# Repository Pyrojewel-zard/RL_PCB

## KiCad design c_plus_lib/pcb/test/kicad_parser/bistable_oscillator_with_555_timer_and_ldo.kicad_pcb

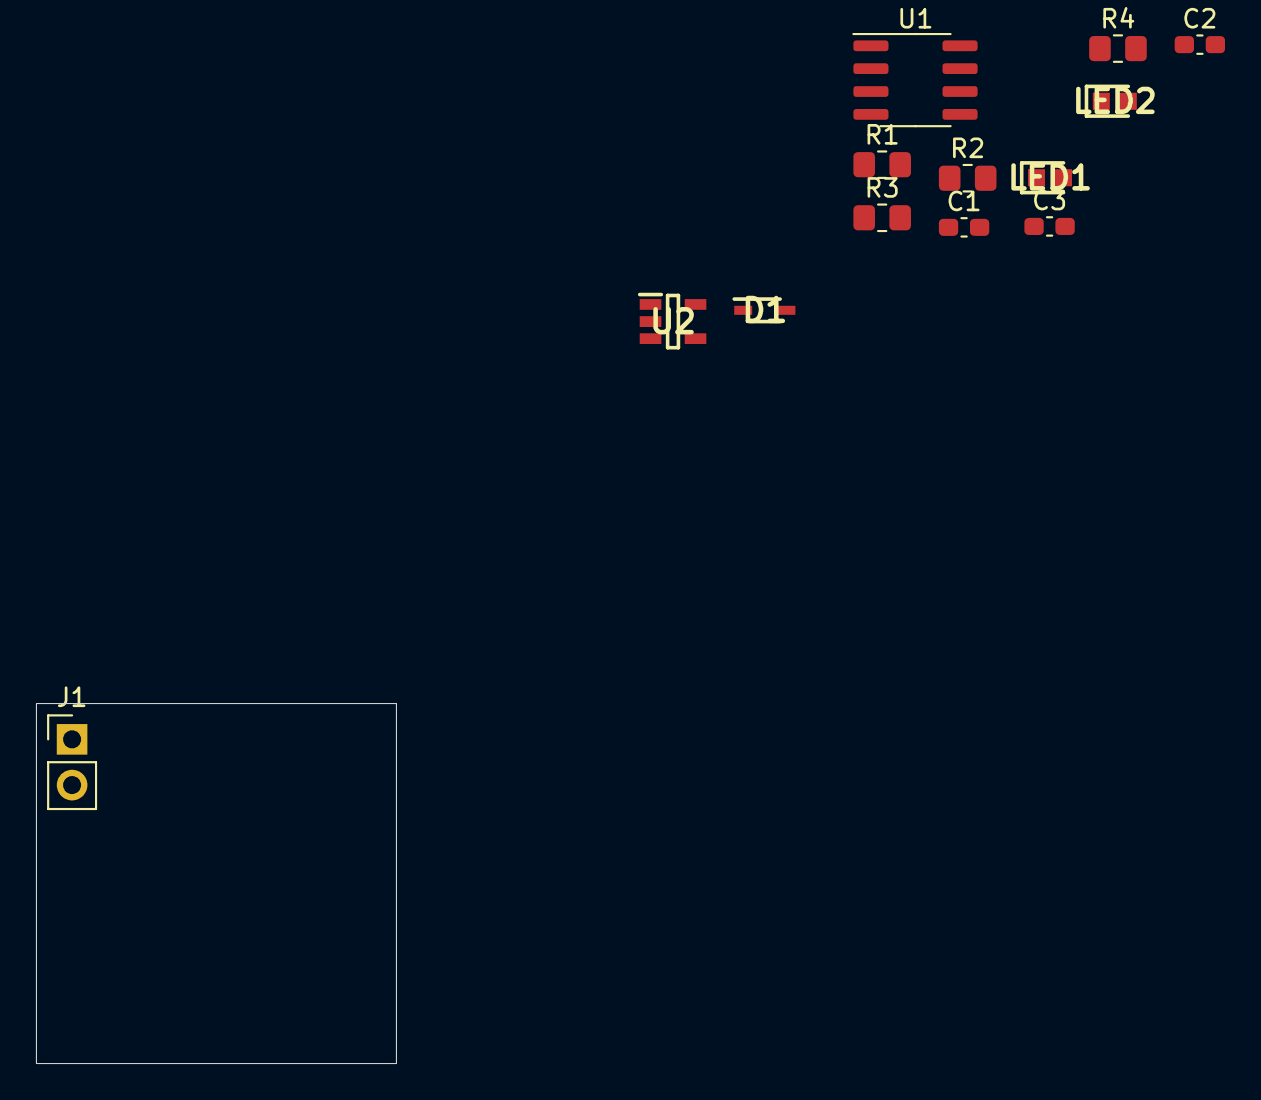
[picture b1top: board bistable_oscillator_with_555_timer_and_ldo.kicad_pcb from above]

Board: 2 copper layers, 20.0 x 20.0 mm, 13 parts (0 on the bottom side), 9 nets, no tracks yet.

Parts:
C1, C2, C3: 1uF; C_0603_1608Metric_Pad1.08x0.95mm_HandSolder
D1: NSR0530HT1G; SOD2512X110N
J1: Conn_01x02_Male; PinHeader_1x02_P2.54mm_Vertical
LED1, LED2: 150060VS75000; LEDC1608X80N
R1, R4: 2k; R_0805_2012Metric_Pad1.20x1.40mm_HandSolder
R2: 47k; R_0805_2012Metric_Pad1.20x1.40mm_HandSolder
R3: 120k; R_0805_2012Metric_Pad1.20x1.40mm_HandSolder
U1: NE555D; SOIC-8_3.9x4.9mm_P1.27mm
U2: TPS7A2033PDBVR; SOT95P280X145-5N

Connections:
+3V3: C2.1, R1.1, R2.1, U1.4, U1.8, U2.5
GND: C1.2, C2.2, C3.2, J1.2, LED1.1, LED2.1, U1.1, U2.2
unnamed: C1.1, D1.1, U2.1, U2.3
unnamed: C3.1, R3.2, U1.2, U1.6
unnamed: D1.2, J1.1
unnamed: LED1.2, R1.2
unnamed: LED2.2, R4.2
unnamed: R2.2, R3.1, U1.7
unnamed: R4.1, U1.3

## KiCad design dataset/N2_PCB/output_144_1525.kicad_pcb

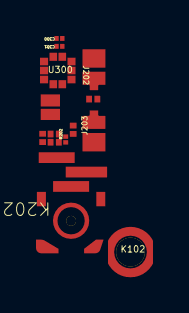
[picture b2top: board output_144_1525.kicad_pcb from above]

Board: 2 copper layers, 14 parts (0 on the bottom side), 7 nets, no tracks yet.

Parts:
C204: CAP_NP_CAP0201-HT0_33_33PF; CAP0201-HT0_33
C300, C301: CAP_NP_CAP01005_HT0_22_S0_38_0.; CAP01005_HT0_22_S0_38
EM200, EM201: CAP_NP_CAP0201-HT0_33_100PF; CAP0201-HT0_33
J110: KEY_2P_ANT_1_0X1_7_P2_HT1_45_HD; ANT_1_0X1_7_P2_HT1_45_HD
J202, J203: KEY_2P_ANT_2_7X1_2_P2_HT2_15_HD; ANT_2_7X1_2_P2_HT2_15_HD
K102: NUT_PAD-RING-TYPE-C_N2_PAD-RING; PAD-RING-TYPE-C_N2
K202: NUT_STIFFER-STEEL-MIC_N2_STIFFE; STIFFER-STEEL-MIC_N2
R202: RES_RES01005_HT0_15_S0_38_0OHM; RES01005_HT0_15_S0_38
R203, R204: RES_RES0201-HT0_23_HD_0OHM; RES0201-HT0_23_HD
U300: BMP580_HLGASQ2_0_PS0_5-HT0_8_P1; HLGASQ2_0_PS0_5-HT0_8_P10_HD

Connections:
CDC_MIC3_N: C204.2, R204.2
CDC_MIC3_P: C204.1, R203.2
GND: C300.2, C301.2, EM200.2, EM201.2, J110.1, J110.2, K102.1, K202.1, R202.2, U300.3, U300.5, U300.7, U300.8, U300.9
HAP_OUT_M: EM200.1, J203.1, J203.2
HAP_OUT_P: EM201.1, J202.1, J202.2
N17757331: R202.1, R204.1
VREG_L1B_1P8: C300.1, C301.1, U300.1, U300.6, U300.10

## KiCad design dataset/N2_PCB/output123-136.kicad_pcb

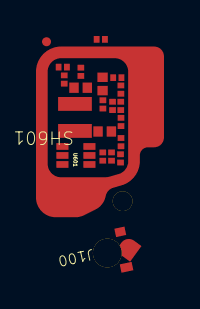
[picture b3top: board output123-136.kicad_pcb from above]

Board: 2 copper layers, 21 parts (0 on the bottom side), 7 nets, no tracks yet.

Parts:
A144: RES_RES0201-HT0_23_HD_0OHM; RES0201-HT0_23_HD
C612: CAP_NP_CAP0201-HT0_33_10PF; CAP0201-HT0_33
C613, C623: CAP_NP_CAP0402-HT0_7_10UF; CAP0402-HT0_7
C614: CAP_NP_CAP0402-HT0_7_22UF; CAP0402-HT0_7
C615, C616, C617, C621, C622: CAP_NP_CAP0201-HT0_35_1UF; CAP0201-HT0_35
C619: CAP_NP_CAP0201-HT0_39_1UF; CAP0201-HT0_39
C620: CAP_NP_CAP0201-HT0_33_0.47UF; CAP0201-HT0_33
J100: SPRING_3P_ANT_2_6X2_99_P3_HT0_5; ANT_2_6X2_99_P3_HT0_58_HD
L600: INDUCTOR_IND2_0X1_6_P1_5_HT1_0_; IND2_0X1_6_P1_5_HT1_0_HD
R601: RES_RES0201-HT0_23_HD_75K; RES0201-HT0_23_HD
R602: RES_RES0201-HT0_23_HD_90.9KOHM; RES0201-HT0_23_HD
R603, R606: RES_NM_RES0201-HT0_28_HD_NM_NM; RES0201-HT0_28_HD_NM
R604: RES_RES0201-HT0_23_HD_10KOHM; RES0201-HT0_23_HD
SH601: SHIELDING_KINE-SHIELDING-FRAME_; KINE-SHIELDING-FRAME_N2
U601: WD10721_DFNSQ1_6_PS0_5_HT0_6_P6; DFNSQ1_6_PS0_5_HT0_6_P6_HD

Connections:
GND: C613.2, C614.2, C615.2, C616.2, C617.2, C619.2, C620.2, C621.2, C622.2, C623.2, R602.2, SH601.1, U601.2
N17753229: J100.1, J100.2, J100.3
N17988891: L600.1, U601.4
N17989092: C612.1, R601.1, R602.1, U601.1
OLED_DVDD: C612.2, C614.1, C621.1, C623.1, L600.2, R601.2, R606.1
TP_1P8: C620.1, R603.2, R604.2
VPH_PWR: C613.1, U601.3

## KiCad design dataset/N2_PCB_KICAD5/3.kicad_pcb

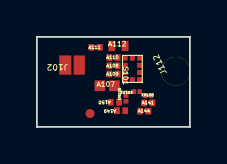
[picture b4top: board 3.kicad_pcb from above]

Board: 2 copper layers, 8.5 x 5.0 mm, 16 parts (0 on the bottom side), 10 nets, no tracks yet.

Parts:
A107: INDUCTOR_IND0402CS-HT0_6_FPC_S_; IND0402CS-HT0_6_FPC_S_1
A108: CAP_NP_CAP0201-HT0_33_1.6PF; CAP0201-HT0_33_24
A109: CAP_NP_CAP0201-HT0_33_2.7PF; CAP0201-HT0_33_26
A110: INDUCTOR_IND0201-HT0_35_15NH; IND0201-HT0_35_7
A111: CAP_NP_CAP0201-HT0_33_33PF; CAP0201-HT0_33_23
A112: INDUCTOR_IND0402CS-HT0_6_10NH; IND0402CS-HT0_6_4
A141: RES_RES0201-HT0_23_HD_0OHM; RES0201-HT0_23_HD_27
A144: RES_RES0201-HT0_23_HD_0OHM; RES0201-HT0_23_HD_28
A149: RES_RES0201-HT0_23_HD_10OHM; RES0201-HT0_23_HD_32
A150: CAP_NP_CAP0201-HT0_33_100NF; CAP0201-HT0_33_25
EM100: RES_NM_RES01005_HT0_15_S0_38_NM; RES01005_HT0_15_S0_38_NM_1
EM101: RES_NM_RES01005_HT0_15_S0_38_NM; RES01005_HT0_15_S0_38_NM_2
EM105: CAP_NM_CAP01005_HT0_22_NM_NM; CAP01005_HT0_22_NM_3
J102: KEY_2P_ANT_1_7X1_0_P2_HT1_35_HD; ANT_1_7X1_0_P2_HT1_35_HD_1
J112: ANT_PIN_ANT_HG_F1_XM-217-XC-186; ANT_HG_F1_1
S101: QM13344_SMT1_1X1_5_HT0_45_10P_H; SMT1_1X1_5_HT0_45_10P_HD_1

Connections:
GND: A112.2, A150.2, EM100.2, EM101.2, EM105.2, S101.5, S101.10
N17753661: A149.2, A150.1, EM105.1, S101.3, S101.4
N17753743: A111.1, J102.1, J102.2
N17753749: A107.1, A108.1, A109.1, A110.1, A111.2, A112.1
N17753816: A109.2, S101.8
N17753880: A108.2, S101.7
N17753882: A141.1, EM100.1, S101.2
N17753954: A144.1, EM101.1, S101.1
N17837242: A110.2, S101.6
N17837274: A107.2, S101.9

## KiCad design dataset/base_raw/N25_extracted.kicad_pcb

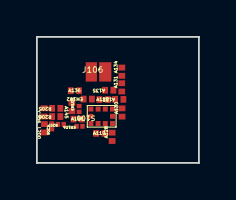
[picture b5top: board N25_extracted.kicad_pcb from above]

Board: 2 copper layers, 9.0 x 7.0 mm, 22 parts (0 on the bottom side), 15 nets, no tracks yet.

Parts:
A118: INDUCTOR_IND0201-HT0_35_11NH; IND0201-HT0_35_2
A119: INDUCTOR_IND0201-HT0_35_5.6NH; IND0201-HT0_35_3
A122: INDUCTOR_IND0201-HT0_35_1NH; IND0201-HT0_35_1
A128: INDUCTOR_IND0201-HT0_42_3NH; IND0201-HT0_42_1
A130: CAP_NP_CAP0201-HT0_33_0.4PF; CAP0201-HT0_33_1
A131: RES_RES0201-HT0_23_HD_0OHM; RES0201-HT0_23_HD_1
A134: CAP_NM_CAP0201-HT0_33_NM_NM; CAP0201-HT0_33_NM_1
A135: CAP_NM_CAP0201-HT0_33_NM_NM; CAP0201-HT0_33_NM_2
A136: RES_RES0201-HT0_23_HD_0OHM; RES0201-HT0_23_HD_4
A145: RES_RES0201-HT0_23_HD_0OHM; RES0201-HT0_23_HD_2
A146: RES_RES0201-HT0_23_HD_0OHM; RES0201-HT0_23_HD_3
C205: CAP_NP_CAP0201-HT0_33_33PF; CAP0201-HT0_33_4
C206: CAP_NP_CAP01005_HT0_22_S0_38_0.; CAP01005_HT0_22_S0_38_1
EM102: CAP_NP_CAP0201-HT0_33_100PF; CAP0201-HT0_33_3
EM103: CAP_NM_CAP01005_HT0_22_NM_NM; CAP01005_HT0_22_NM_1
EM104: CAP_NM_CAP01005_HT0_22_NM_NM; CAP01005_HT0_22_NM_2
J106: KEY_2P_ANT_1_0X1_7_P2_HT1_45_HD; ANT_1_0X1_7_P2_HT1_45_HD_1
L200: INDUCTOR_IND0201-HT0_35_180NH; IND0201-HT0_35_4
R205: RES_RES0201-HT0_23_HD_0OHM; RES0201-HT0_23_HD_5
R206: RES_RES0201-HT0_23_HD_0OHM; RES0201-HT0_23_HD_6
R207: RES_RES01005_HT0_15_S0_38_0OHM; RES01005_HT0_15_S0_38_1
S100: QM13145_SMT1_2X1_6_PS0_4-HT0_5_; SMT1_2X1_6_PS0_4-HT0_5_P10_H6C

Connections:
CDC_MIC4_N: C205.2, R206.2
CDC_MIC4_P: C205.1, R205.2
GND: A118.1, A119.1, A128.1, A134.2, A135.2, C206.2, EM102.2, EM103.2, EM104.2, J106.1, J106.2, R207.2, S100.7
N17753078: A122.1, A130.2, A131.1, A135.1
N17753084: A122.2, S100.1
N17753221: A119.2, S100.8
N17753329: A118.2, S100.2
N17753375: A128.2, S100.9
N17753406: A136.2, EM102.1, S100.3, S100.4
N17753412: A130.1, S100.10
N17753435: A145.2, EM103.1, S100.5
N17753447: A146.2, EM104.1, S100.6
N17753582: A131.2, A134.1
N17757493: R206.1, R207.1
WCD_MIC_BIAS4: C206.1, L200.1

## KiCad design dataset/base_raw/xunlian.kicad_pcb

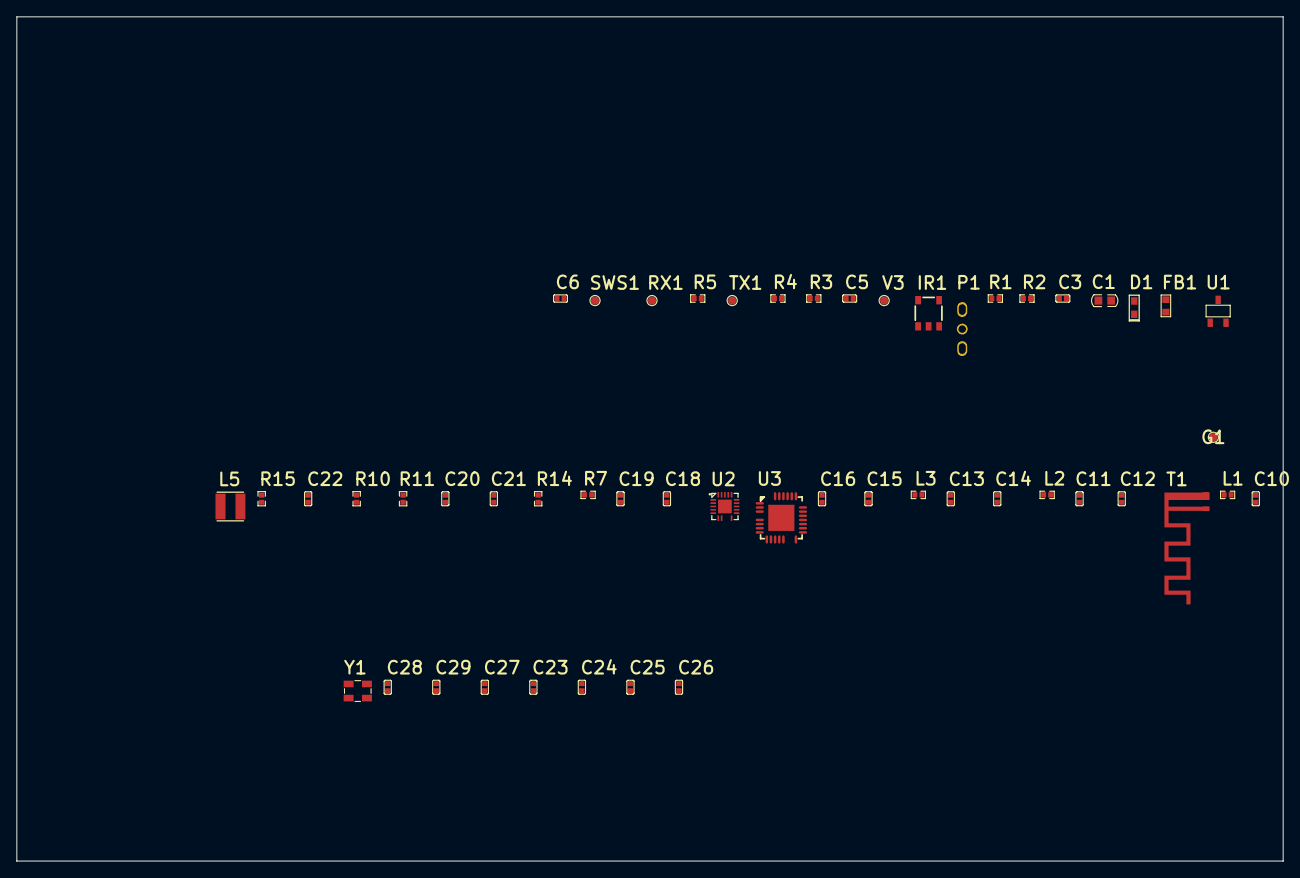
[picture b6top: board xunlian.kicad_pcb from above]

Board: 2 copper layers, 152.4 x 101.6 mm, 51 parts (0 on the bottom side), 39 nets, no tracks yet.

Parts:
C1: 10uF/16V; C0603
C3, C13, C21, C28: 10uF; C0402
C5, C14, C29: 100nF; C0402
C6: 10nF; C0402
C10: 220pF; C0402
C11: 2.2uF; C0402
C12, C16, C18, C22, C24, C25, C26, C27: 1uF; C0402
C15: 18pF; C0402
C19, C20: 1nF; C0402
C23: 33nF; C0402
D1: PT19-21C; LED0603
FB1: GZ1608; R0603
G1: GND; D
IR1: LF0038Q; SMT-IRM
L1: 0R; R0402
L2: NC/1.3nH; R0402
L3: 1nH; R0402
L5: 47uH; L3015
P1: 3P; 3P-2.54
R1, R5: 100R; R0402
R2: 39K; R0402
R3: 47k; R0402
R4, R11: 1K; R0402
R7, R14: 10k; R0402
R10, R15: 0; R0402
RX1: T; D
SWS1: RST; D
T1: TP; BLE_ANT_M
TX1: R; D
U1: LR8103A-T33; SOT23-3-L
U2: XBR818; QFN20_3x3
U3: TLSR8359F512ET32; QFN32
V3: 3V3; D
Y1: 32MHz; SMD3225

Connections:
1V2: C11.1, C12.1, C28.1, C29.1, U3.12, U3.28
3.3V: C3.1, C13.1, C14.2, C22.1, C26.1, D1.2, R1.2, R2.2, R14.1, U1.2, U2.18, U3.9, U3.18, U3.19, V3.1
5V: FB1.1, P1.3
AD: C23.1, R15.2, U3.6
CDS: C5.1, D1.1, R3.2, U3.16
GND: C1.2, C3.2, C5.2, C6.1, C11.2, C12.2, C13.2, C14.1, C15.2, C16.2, C18.2, C19.2, C21.2, C22.2, C23.2, C24.2, C25.2, C26.2, C27.2, C28.2, C29.2, G1.1, IR1.4, L3.2, P1.1, R3.1, R7.1, R10.1, U1.1, U2.5, U2.17, U2.21, U3.7, U3.33, Y1.2, Y1.4
I2C_SCL: U2.12, U3.21
I2C_SDA: U2.11, U3.20
IR: C6.2, R5.1, U3.23
MCU-OUT: R4.1, U3.1
NetC1_1: C1.1, FB1.2, U1.3
NetC10_1: C10.1, L2.2, U3.27
NetC10_2: C10.2, L1.1
NetC15_1: C15.1, L2.1, U3.26
NetC18_1: C18.1, U2.3
NetC19_1: C19.1, U2.2
NetC20_1: C20.1, R15.1, U2.20
NetC20_2: C20.2, R11.2, U2.1
NetC21_1: C21.1, R11.1
NetC24_1: C24.1, U2.19
NetC25_1: C25.1, U3.8
NetC27_1: C27.1, U3.13
NetIR1_3: IR1.3, R2.1, R5.2
NetIR1_5: IR1.5, R1.1
NetL1_2: L1.2, T1.1
NetL5_1: L5.1, U3.11
NetL5_2: L5.2, U3.10
NetR7_2: R7.2, U2.14
NetR14_2: R14.2, U2.13
NetU2_15: U2.15, U2.16
O: P1.2, R4.2
RF_TX: L3.1, U2.6
RST: C16.1, U3.25
RX: RX1.1, U3.3
SWS: SWS1.1, U3.5
TX: TX1.1, U3.2
VRE: R10.2, U3.22
XTAL1: U3.29, Y1.3
XTAL2: U3.30, Y1.1

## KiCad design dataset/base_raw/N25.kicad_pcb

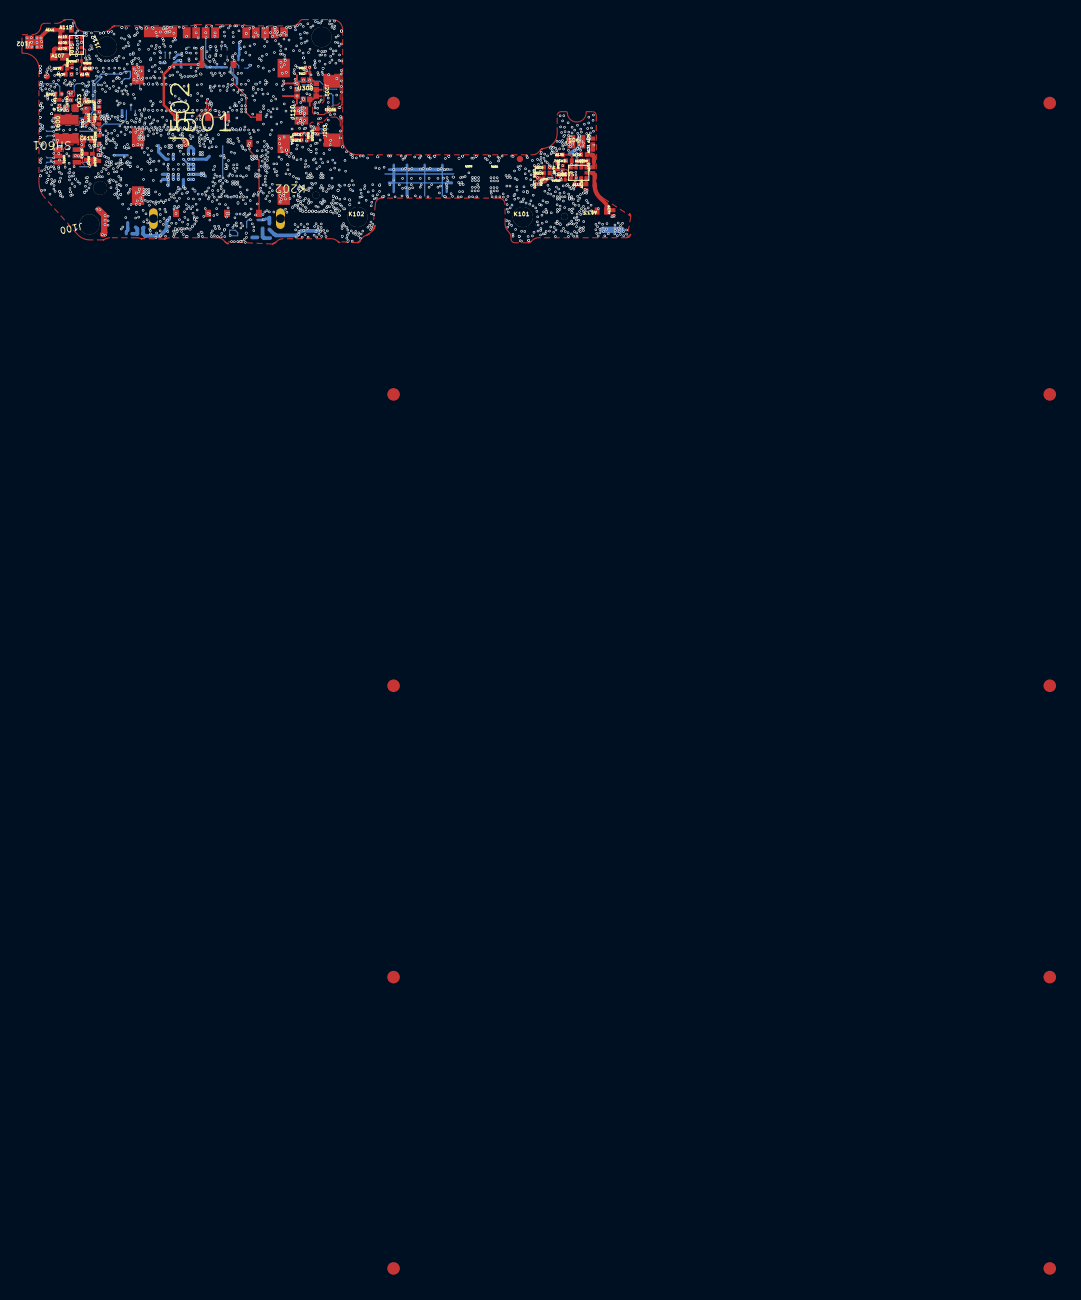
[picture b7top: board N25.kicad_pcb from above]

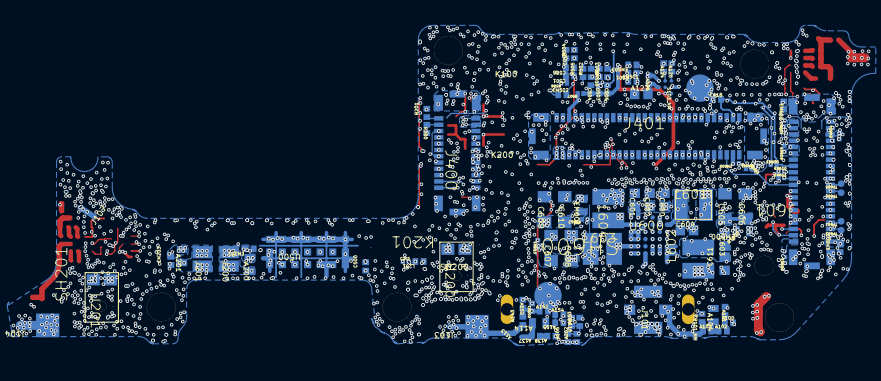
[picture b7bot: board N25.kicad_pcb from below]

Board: 6 copper layers, 187 parts (108 on the bottom side), 133 nets.

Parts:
A100: CAP_NP_CAP0201-HT0_33_33PF; CAP0201-HT0_33_19
A101: INDUCTOR_IND0201-HT0_35_100NH; IND0201-HT0_35_6
A102: RES_RES0201-HT0_23_HD_0OHM; RES0201-HT0_23_HD_26
A103: RES_RES0201-HT0_23_HD_0OHM; RES0201-HT0_23_HD_25
A104: INDUCTOR_IND0402CS-HT0_6_3.6NH; IND0402CS-HT0_6_3
A105: CAP_NP_CAP0201-HT0_33_56PF; CAP0201-HT0_33_14
A107: INDUCTOR_IND0402CS-HT0_6_FPC_S_; IND0402CS-HT0_6_FPC_S_1
A108: CAP_NP_CAP0201-HT0_33_1.6PF; CAP0201-HT0_33_24
A109: CAP_NP_CAP0201-HT0_33_2.7PF; CAP0201-HT0_33_26
A110: INDUCTOR_IND0201-HT0_35_15NH; IND0201-HT0_35_7
A111: CAP_NP_CAP0201-HT0_33_33PF; CAP0201-HT0_33_23
A112: INDUCTOR_IND0402CS-HT0_6_10NH; IND0402CS-HT0_6_4
A113: CAP_NP_CAP0201-HT0_33_33PF; CAP0201-HT0_33_11
A114: INDUCTOR_IND0402CS-HT0_6_18NH; IND0402CS-HT0_6_2
A115: RES_RES0201-HT0_23_HD_0OHM; RES0201-HT0_23_HD_15
A116: RES_RES0201-HT0_23_HD_0OHM; RES0201-HT0_23_HD_14
A118: INDUCTOR_IND0201-HT0_35_11NH; IND0201-HT0_35_2
A119: INDUCTOR_IND0201-HT0_35_5.6NH; IND0201-HT0_35_3
A122: INDUCTOR_IND0201-HT0_35_1NH; IND0201-HT0_35_1
A124: RES_RES0201-HT0_23_HD_560OHM; RES0201-HT0_23_HD_20
A125: RES_RES0201-HT0_23_HD_560OHM; RES0201-HT0_23_HD_24
A126: CAP_NP_CAP0201-HT0_35_1UF; CAP0201-HT0_35_2
A127: CAP_NM_CAP0402-HT0_5_NM_NM; CAP0402-HT0_5_NM_1
A128: INDUCTOR_IND0201-HT0_42_3NH; IND0201-HT0_42_1
A129: CAP_NP_CAP0201-HT0_33_1.8PF; CAP0201-HT0_33_2
A130: CAP_NP_CAP0201-HT0_33_0.4PF; CAP0201-HT0_33_1
A131: RES_RES0201-HT0_23_HD_0OHM; RES0201-HT0_23_HD_1
A133: INDUCTOR_IND0402CS-HT0_6_3.9NH; IND0402CS-HT0_6_1
A134: CAP_NM_CAP0201-HT0_33_NM_NM; CAP0201-HT0_33_NM_1
A135: CAP_NM_CAP0201-HT0_33_NM_NM; CAP0201-HT0_33_NM_2
A136: RES_RES0201-HT0_23_HD_0OHM; RES0201-HT0_23_HD_4
A137: CAP_NM_CAP0201-HT0_33_NM_NM; CAP0201-HT0_33_NM_4
A138: CAP_NM_CAP0201-HT0_33_NM_NM; CAP0201-HT0_33_NM_3
A141: RES_RES0201-HT0_23_HD_0OHM; RES0201-HT0_23_HD_27
A142: RES_RES0201-HT0_23_HD_0OHM; RES0201-HT0_23_HD_13
A143: INDUCTOR_IND0201-HT0_42_100NH; IND0201-HT0_42_2
A144: RES_RES0201-HT0_23_HD_0OHM; RES0201-HT0_23_HD_28
A145: RES_RES0201-HT0_23_HD_0OHM; RES0201-HT0_23_HD_2
A146: RES_RES0201-HT0_23_HD_0OHM; RES0201-HT0_23_HD_3
A149: RES_RES0201-HT0_23_HD_10OHM; RES0201-HT0_23_HD_32
A150: CAP_NP_CAP0201-HT0_33_100NF; CAP0201-HT0_33_25
A152: CAP_NP_CAP0201-HT0_33_5PF; CAP0201-HT0_33_10
A153: RES_NM_RES0201-HT0_28_HD_NM_NM; RES0201-HT0_28_HD_NM_2
A154: RES_NM_RES0201-HT0_28_HD_NM_NM; RES0201-HT0_28_HD_NM_1
A200: INDUCTOR_IND0402CS-HT0_60_34NH; IND0402CS-HT0_60_2
A201: INDUCTOR_IND0402CS-HT0_60_34NH; IND0402CS-HT0_60_1
A202: CAP_NP_CAP0201-HT0_33_56PF; CAP0201-HT0_33_17
C202: CAP_NP_CAP01005_HT0_22_S0_38_0.; CAP01005_HT0_22_S0_38_2
C204: CAP_NP_CAP0201-HT0_33_33PF; CAP0201-HT0_33_9
C205: CAP_NP_CAP0201-HT0_33_33PF; CAP0201-HT0_33_4
C206: CAP_NP_CAP01005_HT0_22_S0_38_0.; CAP01005_HT0_22_S0_38_1
C300: CAP_NP_CAP01005_HT0_22_S0_38_0.; CAP01005_HT0_22_S0_38_3
C301: CAP_NP_CAP01005_HT0_22_S0_38_0.; CAP01005_HT0_22_S0_38_4
C500: CAP_NP_CAP0201-HT0_35_1UF; CAP0201-HT0_35_1
C501: CAP_NP_CAP0201-HT0_33_33PF; CAP0201-HT0_33_13
C502: CAP_NP_CAP0201-HT0_35_1UF; CAP0201-HT0_35_2
C503: CAP_NP_CAP0201-HT0_33_33PF; CAP0201-HT0_33_15
C504: CAP_NP_CAP0201-HT0_35_1UF; CAP0201-HT0_35_3
C505: CAP_NP_CAP0201-HT0_33_100NF; CAP0201-HT0_33_16
C506: CAP_NP_CAP0201-HT0_33_100NF; CAP0201-HT0_33_12
C600, C601, C602, C603: CAP_NP_CAP0402-HT0_7_10UF; CAP0402-HT0_7_1
C604: CAP_NP_CAP0402-HT0_7_10UF; CAP0402-HT0_7_2
C605, C606: CAP_NP_CAP0603-HT1_00_10UF; CAP0603-HT1_00_2
C607, C608, C609, C610: CAP_NP_CAP0603-HT1_00_22UF; CAP0603-HT1_00_1
C611: CAP_NP_CAP0402-HT0_7_10UF; CAP0402-HT0_7_3
C612: CAP_NP_CAP0201-HT0_33_10PF; CAP0201-HT0_33_21
C613: CAP_NP_CAP0402-HT0_7_10UF; CAP0402-HT0_7_5
C614: CAP_NP_CAP0402-HT0_7_22UF; CAP0402-HT0_7_6
C615, C621: CAP_NP_CAP0201-HT0_35_1UF; CAP0201-HT0_35_5
C616: CAP_NP_CAP0201-HT0_35_1UF; CAP0201-HT0_35_6
C617, C622: CAP_NP_CAP0201-HT0_35_1UF; CAP0201-HT0_35_7
C618: CAP_NP_CAP0201-HT0_35_1UF; CAP0201-HT0_35_4
C619: CAP_NP_CAP0201-HT0_39_1UF; CAP0201-HT0_39_1
C620: CAP_NP_CAP0201-HT0_33_0.47UF; CAP0201-HT0_33_22
C623: CAP_NP_CAP0402-HT0_7_10UF; CAP0402-HT0_7_4
CR100: ESD_ESD0_6X0_3_PS0_425HT0_32_HD; ESD0_6X0_3_PS0_425HT0_32_HD_1
CR101_NM: CAP_NP_CAP0201-HT0_33_1.2PF; CAP0201-HT0_33_18
EM100: RES_NM_RES01005_HT0_15_S0_38_NM; RES01005_HT0_15_S0_38_NM_1
EM101: RES_NM_RES01005_HT0_15_S0_38_NM; RES01005_HT0_15_S0_38_NM_2
EM102: CAP_NP_CAP0201-HT0_33_100PF; CAP0201-HT0_33_3
EM103: CAP_NM_CAP01005_HT0_22_NM_NM; CAP01005_HT0_22_NM_1
EM104: CAP_NM_CAP01005_HT0_22_NM_NM; CAP01005_HT0_22_NM_2
EM105: CAP_NM_CAP01005_HT0_22_NM_NM; CAP01005_HT0_22_NM_3
EM200: CAP_NP_CAP0201-HT0_33_100PF; CAP0201-HT0_33_8
EM201: CAP_NP_CAP0201-HT0_33_100PF; CAP0201-HT0_33_7
EM202: CAP_NP_CAP0201-HT0_33_100PF; CAP0201-HT0_33_6
EM203: CAP_NP_CAP0201-HT0_33_100PF; CAP0201-HT0_33_5
EM400, EM611: CAP_NP_CAP01005_HT0_22_S0_38_15; CAP01005_HT0_22_S0_38_7
EM401: CAP_NP_CAP01005_HT0_22_S0_38_33; CAP01005_HT0_22_S0_38_9
EM500: RES_RES0201-HT0_23_HD_51OHM; RES0201-HT0_23_HD_19
EM501: RES_RES0201-HT0_23_HD_100OHM; RES0201-HT0_23_HD_21
EM502: RES_RES0201-HT0_23_HD_100OHM; RES0201-HT0_23_HD_12
EM503: RES_RES0201-HT0_23_HD_51OHM; RES0201-HT0_23_HD_23
EM600: BEAD_BEAD1_0X0_5P0_25-HT0_5_120; BEAD1_0X0_5P0_25-HT0_5_2
EM601: BEAD_BEAD1_0X0_5P0_25-HT0_5_120; BEAD1_0X0_5P0_25-HT0_5_1
EM602: CAP_NP_CAP0201-HT0_33_150PF; CAP0201-HT0_33_20
EM603, EM609, EM613: CAP_NP_CAP01005_HT0_22_S0_38_15; CAP01005_HT0_22_S0_38_5
EM604: CAP_NP_CAP01005_HT0_22_S0_38_15; CAP01005_HT0_22_S0_38_11
EM605, EM610: CAP_NP_CAP01005_HT0_22_S0_38_15; CAP01005_HT0_22_S0_38_8
EM606: CAP_NP_CAP01005_HT0_22_S0_38_15; CAP01005_HT0_22_S0_38_10
EM607: CAP_NP_CAP0201-HT0_33_150PF; CAP0201-HT0_33_27
EM608, EM612: CAP_NP_CAP01005_HT0_22_S0_38_15; CAP01005_HT0_22_S0_38_6
J100: SPRING_3P_ANT_2_6X2_99_P3_HT0_5; ANT_2_6X2_99_P3_HT0_58_HD_1
J101: RF_CON_4P_CN_RF_4P_2X2_HT0_66_8; CN_RF_4P_2X2_HT0_66_2
J102: KEY_2P_ANT_1_7X1_0_P2_HT1_35_HD; ANT_1_7X1_0_P2_HT1_35_HD_1
J103: SPRING_2P_ANT2_75X2_4_P2_HT0_95; ANT2_75X2_4_P2_HT0_95_HD_2
J104: SPRING_2P_ANT2_75X2_4_P2_HT0_95; ANT2_75X2_4_P2_HT0_95_HD_1
J106: KEY_2P_ANT_1_0X1_7_P2_HT1_45_HD; ANT_1_0X1_7_P2_HT1_45_HD_1
J107: RF_CON_4P_CN_RF_4P_2X2_HT0_66_8; CN_RF_4P_2X2_HT0_66_1
J110: KEY_2P_ANT_1_0X1_7_P2_HT1_45_HD; ANT_1_0X1_7_P2_HT1_45_HD_3
J112: ANT_PIN_ANT_HG_F1_XM-217-XC-186; ANT_HG_F1_1
J200, J201: KEY_2P_ANT_1_0X1_7_P2_HT1_45_HD; ANT_1_0X1_7_P2_HT1_45_HD_2
J202: KEY_2P_ANT_2_7X1_2_P2_HT2_15_HD; ANT_2_7X1_2_P2_HT2_15_HD_2
J203: KEY_2P_ANT_2_7X1_2_P2_HT2_15_HD; ANT_2_7X1_2_P2_HT2_15_HD_1
J400: CON_24P_6G_CON24P_2_2X6_75PS0_3; CON24P_2_2X6_75PS0_35_DS_HD_1
J401: 60PIN-6GND_CON60P_2_2X13_05PS0_; CON60P_2_2X13_05PS0_35_DS_HD_1
J501: CAF99-06264-100001_SIM_12_93X15; SIM_12_93X15_85-P18_HT2_38_H51
J502: CAF99-06033-1010_SIM_7_8X13_75_; SIM_7_8X13_75_P12-HT2_65_HD_1
J601: 40-CON_6GND_CON40P_2_2X9_55PS0_; CON40P_2_2X9_55PS0_35_DS_HD_1
K100: NUT_CLIP-DOUBLE-CABLE_N2_314100; CLIP-DOUBLE-CABLE_N2_1
K101, K102: NUT_PAD-RING-TYPE-C_N2_PAD-RING; PAD-RING-TYPE-C_N2_1
K200: NUT_REINFORCE-STEEL-1_N2_REINFO; REINFORCE-STEEL-1_N2_1
K201: NUT_REINFORCE-STEEL-2_N2_REINFO; REINFORCE-STEEL-2_N2_1
K202: NUT_STIFFER-STEEL-MIC_N2_STIFFE; STIFFER-STEEL-MIC_N2_1
L200: INDUCTOR_IND0201-HT0_35_180NH; IND0201-HT0_35_4
L201: INDUCTOR_IND0201-HT0_35_180NH; IND0201-HT0_35_5
L600: INDUCTOR_IND2_0X1_6_P1_5_HT1_0_; IND2_0X1_6_P1_5_HT1_0_HD_1
L601: INDUCTOR_IND2_0X1_6PS1_4-HT1_0_; IND2_0X1_6PS1_4-HT1_0_HD_1
L602: INDUCTOR_IND2_0X1_6P0_8-HT0_8_H; IND2_0X1_6P0_8-HT0_8_HD_3
L603: INDUCTOR_IND2_0X1_6P0_8-HT0_8_H; IND2_0X1_6P0_8-HT0_8_HD_2
L604: INDUCTOR_IND2_0X1_6P0_8-HT0_8_H; IND2_0X1_6P0_8-HT0_8_HD_1
R200: RES_RES0201-HT0_23_HD_4.7KOHM; RES0201-HT0_23_HD_7
R201: RES_RES0201-HT0_23_HD_4.7KOHM; RES0201-HT0_23_HD_8
R202: RES_RES01005_HT0_15_S0_38_0OHM; RES01005_HT0_15_S0_38_2
R203: RES_RES0201-HT0_23_HD_0OHM; RES0201-HT0_23_HD_9
R204: RES_RES0201-HT0_23_HD_0OHM; RES0201-HT0_23_HD_10
R205: RES_RES0201-HT0_23_HD_0OHM; RES0201-HT0_23_HD_5
R206: RES_RES0201-HT0_23_HD_0OHM; RES0201-HT0_23_HD_6
R207: RES_RES01005_HT0_15_S0_38_0OHM; RES01005_HT0_15_S0_38_1
R501: RES_RES0201-HT0_23_HD_100OHM; RES0201-HT0_23_HD_22
R502: RES_RES0201-HT0_23_HD_100OHM; RES0201-HT0_23_HD_17
R503: RES_RES0201-HT0_23_HD_100OHM; RES0201-HT0_23_HD_16
R504: RES_RES0201-HT0_23_HD_1KOHM; RES0201-HT0_23_HD_11
R505: RES_RES0201-HT0_23_HD_100OHM; RES0201-HT0_23_HD_18
R506: RES_RES01005_HT0_15_S0_38_0OHM; RES01005_HT0_15_S0_38_3
R507: RES_RES01005_HT0_15_S0_38_0OHM; RES01005_HT0_15_S0_38_4
R601: RES_RES0201-HT0_23_HD_75K; RES0201-HT0_23_HD_30
R602: RES_RES0201-HT0_23_HD_90.9KOHM; RES0201-HT0_23_HD_29
R603: RES_NM_RES0201-HT0_28_HD_NM_NM; RES0201-HT0_28_HD_NM_4
R604: RES_RES0201-HT0_23_HD_10KOHM; RES0201-HT0_23_HD_31
R606: RES_NM_RES0201-HT0_28_HD_NM_NM; RES0201-HT0_28_HD_NM_3
RT600: THERMISTOR_RES0201-HT0_33_HD_10; RES0201-HT0_33_HD_1
S100: QM13145_SMT1_2X1_6_PS0_4-HT0_5_; SMT1_2X1_6_PS0_4-HT0_5_P10_H6C
S101: QM13344_SMT1_1X1_5_HT0_45_10P_H; SMT1_1X1_5_HT0_45_10P_HD_1
S103_NM: SX9373_WLCSP1_21X1_14_HT0_6_P9_; WLCSP1_21X1_14_HT0_6_P9_HD_1
SH200: SHIELDING_MIC-SHIELDING-2_N2_MI; MIC-SHIELDING-2_N2_1
SH201: SHIELDING_SHIELDING-MIC_J1_MIC_; SHIELDING-MIC_J1_1
SH600: SHIELDING_DC-SHIELDING-FRAME_N2; DC-SHIELDING-FRAME_N2_1
SH601: SHIELDING_KINE-SHIELDING-FRAME_; KINE-SHIELDING-FRAME_N2_1
TP600, TP601, TP602, TP603: T_POINT_S_PAD0_375NSNG_TP0.3_NS; PAD0_375NSNG_1
U200: SPA2629LR5H_MICROPH1_85X2_75-HT; MICROPH1_85X2_75-HT1_0_P3_HD_2
U201: SPA2629LR5H_MICROPH1_85X2_75-HT; MICROPH1_85X2_75-HT1_0_P3_HD_1
U300: BMP580_HLGASQ2_0_PS0_5-HT0_8_P1; HLGASQ2_0_PS0_5-HT0_8_P10_HD_1
U500: N2_FOD_LGA_N2_FOD_LGA_HD_RN2FOD; N2_FOD_LGA_HD_1
U600: NT50379WHB_WLCSPSQ2_455-HT0_675; WLCSPSQ2_455-HT0_675_P36_HD_1
U601: WD10721_DFNSQ1_6_PS0_5_HT0_6_P6; DFNSQ1_6_PS0_5_HT0_6_P6_HD_1
W200: SHORT_SHORT_RES0_06_HD_5_SHORT; SHORT_RES0_06_HD_5_2
W201: SHORT_SHORT_RES0_06_HD_5_SHORT; SHORT_RES0_06_HD_5_1

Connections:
CDC_MIC3_N: C204.2, J401.10, R204.2
CDC_MIC3_P: C204.1, J401.12, R203.2
CDC_MIC4_N: C205.2, J401.18, R206.2
CDC_MIC4_P: C205.1, J401.20, R205.2
DISP0_AVDD_7P6: C605.1, C606.1, C619.1, EM606.1, J601.1, U600.D1
DISP0_ELVDD: C615.1, EM600.2, EM602.1, J601.G1, J601.G2, J601.G3
DISP0_ELVSS: C616.1, EM601.2, EM603.1, J601.2, J601.4, J601.6
DISP_VDDIO_1P8: C617.1, EM604.1, J401.48, J601.5
ERR_INT_N: J401.52, J601.24
FLICKER_PRESSURE_SAR_I2C_SCL: J401.40, S103_NM.A1, U300.2
FLICKER_PRESSURE_SAR_I2C_SDA: J401.42, S103_NM.B1, U300.4
FOD_INT_N: J400.8, U500.13
FOD_RST: J400.10, U500.8
FOD_SPI_CLK: J400.18, U500.10
FOD_SPI_CS: J400.13, U500.11
FOD_SPI_MISO: J400.20, U500.9
FOD_SPI_MOSI: J400.12, U500.12
GND: A101.2, A104.2, A105.2, A112.2, A114.2, A118.1, A119.1, A126.2, A127.2, A128.1, A133.2, A134.2, A135.2, A138.2, A150.2, A152.2, A202.2, C202.2, C206.2, C300.2, C301.2, C500.2, C501.2, C502.2, C503.2, C504.2, C505.2, C506.2, C600.2, C601.2, C602.2, C603.2, C604.2, C605.2, C606.2, C607.2, C608.2, C609.2, C610.2, C611.2, C613.2, C614.2, C615.2, C616.2, C617.2, C618.2, C619.2, C620.2, C621.2, C622.2, C623.2, CR100.2, CR101_NM.2, EM100.2, EM101.2, EM102.2, EM103.2, EM104.2, EM105.2, EM200.2, EM201.2, EM202.2, EM203.2, EM400.2, EM602.2, EM603.2, EM604.2, EM605.2, EM606.2, EM607.2, EM608.2, EM609.2, EM610.2, EM611.2, EM612.2, EM613.2, J101.2, J101.3, J101.4, J106.1, J106.2, J110.1, J110.2, J400.5, J400.6, J400.14, J400.16, J400.G3, J400.G4, J400.G6, J401.1, J401.6, J401.7, J401.13, J401.14, J401.19, J401.22, J401.25, J401.28, J401.31, J401.34, J401.37, J501.A1, J501.A2, J501.A3, J501.A4, J501.A5, J501.A6, J501.A7, J501.A8, J501.A14, J501.A16, J501.A17, J501.A18, J502.S17, J502.S18, J601.7, J601.13, J601.19, J601.25, J601.31, J601.37, J601.G4, J601.G5, J601.G6, K100.1, K101.1, K102.1, K200.1, K201.1, K202.1, L603.2, L604.2, R202.2, R207.2, R602.2, S100.7, S101.5, S101.10, S103_NM.A3, S103_NM.C2, SH200.1, SH201.1, SH600.1, SH601.1, U300.3, U300.5, U300.7, U300.8, U300.9, U500.1, U500.2, U500.3, U500.4, U500.5, U500.6, U500.7, U600.A1, U600.A4, U600.B1, U600.C3, U600.E2, U600.F1, U600.F2, U600.F4, U601.2
HAP_OUT_M: EM200.1, J203.1, J401.2, J401.4
HAP_OUT_P: EM201.1, J202.1, J401.G1, J401.G2, J401.G3
LCD_ID_DET1: J401.54, J601.3
LCD_RESET_N: J401.56, J601.22
MDP_VSYNC_P: J401.51, J601.26, U500.14
MIPI_DSI0_EMI_CLK_M: J401.21, J601.21, TP600.1
MIPI_DSI0_EMI_CLK_P: J401.23, J601.23, TP601.1
MIPI_DSI0_EMI_LANE0_M: J401.33, J601.33, TP602.1
MIPI_DSI0_EMI_LANE0_P: J401.35, J601.35, TP603.1
MIPI_DSI0_EMI_LANE1_M: J401.27, J601.27
MIPI_DSI0_EMI_LANE1_P: J401.29, J601.29
MIPI_DSI0_EMI_LANE2_M: J401.15, J601.15
MIPI_DSI0_EMI_LANE2_P: J401.17, J601.17
MIPI_DSI0_EMI_LANE3_M: J401.9, J601.9
MIPI_DSI0_EMI_LANE3_P: J401.11, J601.11
N17753078: A122.1, A130.2, A131.1, A135.1
N17753084: A122.2, S100.1
N17753221: A119.2, S100.8
N17753235: A100.2, A101.1, A102.1
N17753245: A102.2, A103.1, A104.1
N17753251: A103.2, CR101_NM.1, J101.1
N17753329: A118.2, S100.2
N17753375: A128.2, S100.9
N17753406: A136.2, EM102.1, S100.3, S100.4
N17753412: A129.2, A130.1, A133.1, S100.10
N17753435: A145.2, EM103.1, S100.5
N17753447: A146.2, EM104.1, S100.6
N17753558: A129.1, J104.2
N17753582: A131.2, A134.1
N17753661: A149.2, A150.1, EM105.1, S101.3, S101.4
N17753743: A111.1, J102.1, J102.2
N17753749: A107.1, A108.1, A109.1, A110.1, A111.2, A112.1
N17753816: A109.2, S101.8
N17753880: A108.2, S101.7
N17753882: A141.1, EM100.1, S101.2
N17753954: A144.1, EM101.1, S101.1
N17754187: A143.2, J103.2
N17754197: A114.1, A137.1
N17754439: A142.2, A143.1, A152.1, CR100.1
N17754659: A124.1, S103_NM.B3
N17754673: A124.2, A154.1
N17754732: A125.1, S103_NM.C3
N17754734: A125.2, A153.1
N17757257: R203.1, U200.2
N17757312: L201.2, U200.1
N17757331: R202.1, R204.1, U200.3
N17757419: R205.1, U201.2
N17757474: L200.2, U201.1
N17757493: R206.1, R207.1, U201.3
N17757784: A200.1, J200.1, J200.2
N17757865: A201.1, J201.1, J201.2
N17759260: EM501.1, J501.A10
N17759326: EM503.2, J501.A9
N17759349: J501.A11, R501.2
N17759351: J501.A12, R503.1
N17759372: C501.1, C502.1, C506.1, J501.A15, R506.2
N17759384: J501.A13, R504.1
N17759554: EM500.2, J502.S15, J502.S16
N17759560: J502.S13, J502.S14, R505.1
N17759588: C503.1, C504.1, C505.1, J502.S11, J502.S12, R507.2
N17759596: EM502.1, J502.S21, J502.S22
N17759627: J502.S19, J502.S20, R502.2
N17837242: A110.2, S101.6
N17837274: A107.2, S101.9
N17867861: L601.2, U600.E1
N17867881: L602.2, U600.A2, U600.B2
N17868052: L603.1, U600.B5, U600.B6
N17868089: L604.1, U600.E5, U600.E6
N17868172: C607.1, C608.1, EM600.1, EM613.1, U600.A3, U600.B3, U600.C1
N17868260: C609.1, C610.1, EM601.1, EM612.1, U600.C5, U600.C6, U600.D5, U600.D6, U600.E4
N17988891: L600.1, U601.4
N17989092: C612.1, R601.1, R602.1, U601.1
N17999474: A137.2, A138.1
NFC_SWIO_UICC1: J400.24, R503.2
NFC_SWIO_UICC2: J400.7, R502.1
NFC_VCC_UICC_SIM: J400.17, R506.1
OLED_DVDD: C612.2, C614.1, C621.1, C623.1, EM609.1, J601.10, J601.12, L600.2, R601.2, R606.1
OLED_DVDD_EN: J401.53, U601.5
OLED_DVDD_L11B: J401.50, R606.2
OLED_EL_EN: EM611.1, J601.20, U600.D4
OLED_VDDP_EN: EM610.1, J601.18, U600.D3
SAR_SENSOR0_S: A105.1, A116.1, A153.2, A202.1
SAR_SENSOR1_CS4: A116.2, J401.26
SAR_SENSOR1_CS5: A115.2, J401.24
SAR_SENSOR1_S: A115.1, A142.1, A154.2
SDR_RFFE8_CLK: A141.2, A146.1, J401.32
SDR_RFFE8_DATA: A144.2, A145.1, J401.30
SPK_BOT_OUT_N: A200.2, EM202.1, J400.1, J400.3
SPK_BOT_OUT_P: A201.2, EM203.1, J400.G1, J400.G2, J400.G5
SPK_BOT_SNS_N: J400.4, R200.2
SPK_BOT_SNS_P: J400.2, R201.2
TP_1P8: C620.1, EM607.1, J401.55, J601.39, R603.2, R604.2
TP_3P3: C622.1, EM608.1, J401.58, J601.40
TP_INT_N: J401.39, J601.38, R604.1
TP_RESET_N: J401.49, J601.28, R603.1
TP_SPI_CLK: J401.47, J601.30
TP_SPI_CS: J401.45, J601.32
TP_SPI_MISO: J401.41, J601.36
TP_SPI_MOSI: J401.43, J601.34
UIM1_CLK_1P8: EM503.1, J400.11
UIM1_DATA_1P8: EM501.2, J400.19
UIM1_PRESENT: J400.15, R504.2
UIM1_RESET_1P8: J400.9, R501.1
UIM2_CLK_1P8: EM500.1, J400.22
UIM2_DATA_1P8: EM502.2, J400.21
UIM2_RESET_1P8: J400.23, R505.2
VCI_3P0: C618.1, EM605.1, J401.57, J601.16
VPH_PWR: C600.1, C601.1, C602.1, C603.1, C604.1, C611.1, C613.1, EM400.1, J401.G4, J401.G5, J401.G6, L601.1, L602.1, U600.A5, U600.A6, U600.C2, U600.F5, U600.F6, U601.3
VREG_L1B_1P8: C300.1, C301.1, J401.36, U300.1, U300.6, U300.10
VREG_L4B_1P8: A126.1, A127.1, J401.44, S103_NM.A2
VREG_L7B_1P8: J401.5, R507.1
VREG_L15B_1P8: A136.1, A149.1, J401.46
VREG_L16B_3P0: C500.1, J401.3, U500.15
WCD_MIC_BIAS1: C202.1, J401.8, L201.1
WCD_MIC_BIAS4: C206.1, J401.16, L200.1

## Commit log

2025-05-12 修改注释
2025-05-12 修改torch源为阿里源
2025-07-16 feat: Initial project commit
2025-07-16 feat: Add hpwl算法
2025-07-17 feat: 增加borad处理
2025-07-17 refactor:重构experiment结构，保留必要的一个experiment
2025-07-17 refactor:更新代码架构
2025-07-17 refector:尝试重构C语言模块，发现基本功能较为单一，暂时不需要进行重构
2025-07-17 重构代码
2025-07-17 重构代码2
2025-07-17 feat：python实现原有pcb类，边edge解析存在问题
2025-07-18 refactor: pcb类重构完成，尝试合并到master分支
2025-07-18 C语言实现作为存档
2025-07-18 temp
2025-07-23 refactor-python_pcb
2025-07-23 refactor
2025-07-23 增加C++实现的library到目录下
2025-07-23 回退pcbDraw和environment
2025-07-23 回退training代码到最初版本
2025-07-23 强制指定不同gpu进行训练
2025-07-23 修改python3.9之后不支持的seed的定义
2025-07-28 feat-异形边框（训练完成）
2025-07-29 代码增加注释
2025-07-29 test
2025-07-29 异形边框训练完成
2025-07-29 训练38元件模型
2025-07-29 解决训练的精度问题
2025-07-29 region_7的pcb训练
2025-07-30 整合多个板子
2025-07-30 添加PR删除分支的功能
2025-07-30 修正pcb文件为相对坐标
2025-07-30 原本的对board的解析实现
2025-07-31 修改height和width，模型能正常计算
2025-08-26 0826存档
2025-08-26 workflowchange
2025-09-01 feat: 添加並行 warmup 系統 (warmup存有bug未修复)
    - 新增並行 warmup 管理器，支持多進程數據收集
    - 修改 env_factory 支持 environment 對象傳入
    - 適配 warmup_worker 處理非標準 Gym 環境接口
    - 修改 train.py 集成並行 warmup 功能
    - 添加配置文件和工具腳本
    已知問題：
